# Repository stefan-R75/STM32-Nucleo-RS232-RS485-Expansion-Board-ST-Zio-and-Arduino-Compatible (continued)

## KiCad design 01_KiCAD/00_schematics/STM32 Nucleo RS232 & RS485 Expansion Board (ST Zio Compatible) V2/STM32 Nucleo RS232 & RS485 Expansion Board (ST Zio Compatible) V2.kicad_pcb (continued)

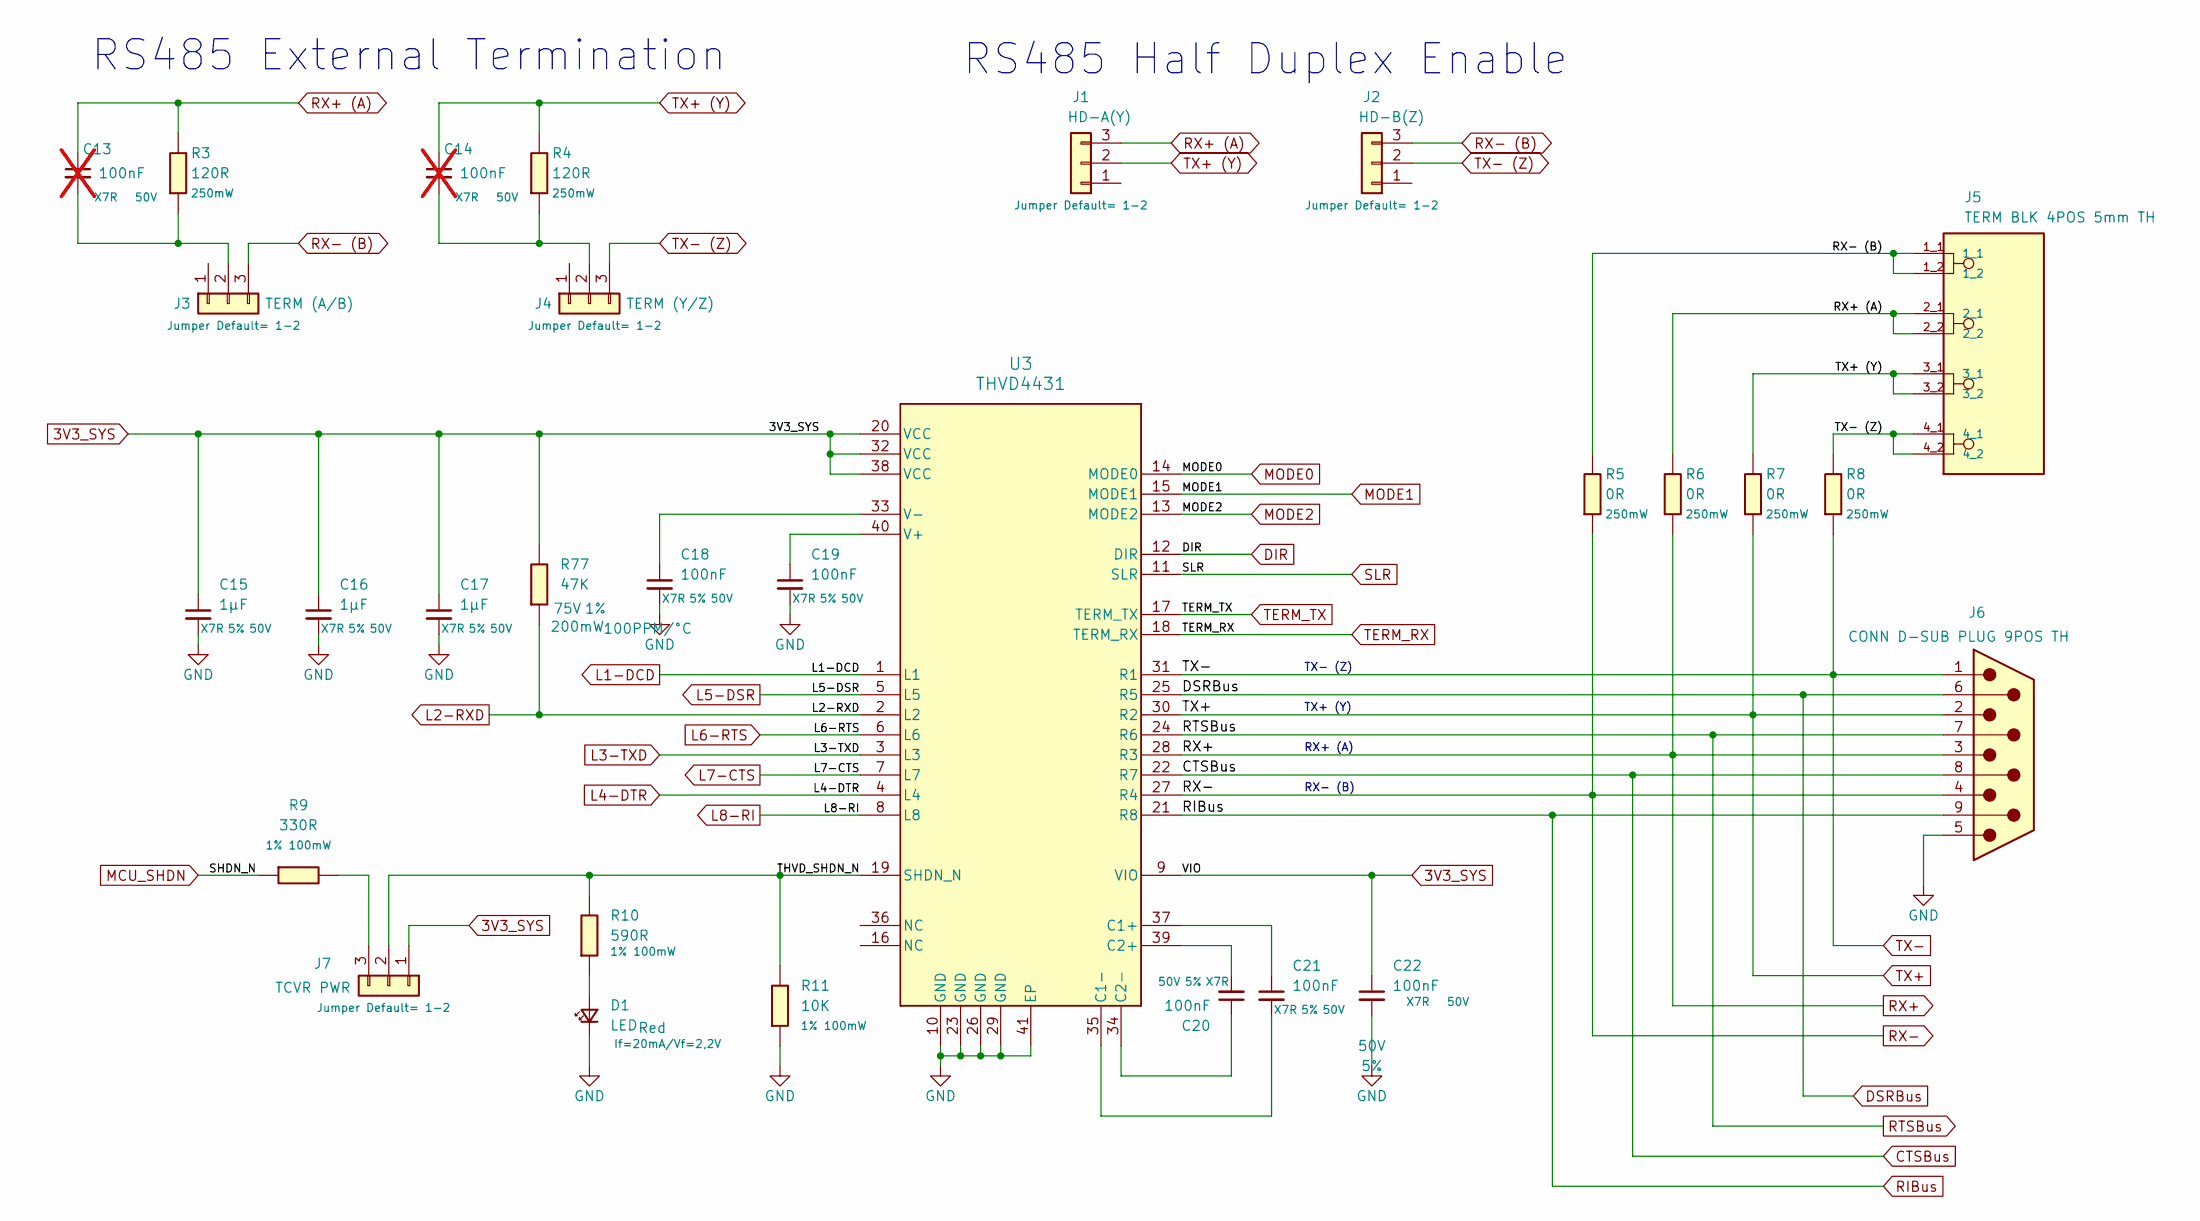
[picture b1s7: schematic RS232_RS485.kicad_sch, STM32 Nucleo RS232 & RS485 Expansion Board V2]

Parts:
C13, C14: 100nF; C_0805_2012Metric; Voltage Rating 50V; Voltage 50V; MPN C0805C104J5RACTU; LCSC C2167095; not fitted
C15, C16, C17: 1µF; C_1206_3216Metric; Voltage 50V; Tolerance 5%; MPN 12065C105JAT2A; LCSC C597503
C18, C19, C20, C21: 100nF; C_0805_2012Metric; Voltage 50V; Tolerance 5%; MPN C0805C104J5RACTU; LCSC C2167095
C22: 100nF; C_0805_2012Metric; Voltage Rating 50V; Voltage 50V; MPN C0805C104J5RACTU; LCSC C2167095
D1: LED; LED_0603_WRE; Voltage Rating If=20mA/Vf=2,2V; Voltage 2,2V; MPN IN-S63ATR; LCSC C6639626
J1: HD-A(Y); Samtec HTSW-103-07-F-S; Voltage Rating Jumper Default= 1-2; MPN HTSW-103-07-G-S; LCSC C5714562
J2: HD-B(Z); Samtec HTSW-103-07-F-S; Voltage Rating Jumper Default= 1-2; MPN HTSW-103-07-F-S; LCSC C5714562
J3: TERM (A/B); Samtec HTSW-103-07-F-S; Voltage Rating Jumper Default= 1-2; MPN HTSW-103-07-F-S; LCSC C5714562
J4: TERM (Y/Z); Samtec HTSW-103-07-F-S; Voltage Rating Jumper Default= 1-2; MPN HTSW-103-07-F-S; LCSC C5714562
J5: TERM BLK 4POS 5mm TH; PHOENIX_1190299; MPN 1190299; LCSC C3309834
J6: CONN D-SUB PLUG 9POS TH; CONN9_2301843-2_TEC; MPN 2301843-2; LCSC C591554
J7: TCVR PWR; Samtec HTSW-103-07-F-S; Voltage Rating Jumper Default= 1-2; MPN HTSW-103-07-F-S; LCSC C5714562
R3, R4: 120R; R_0603; Voltage Rating 250mW; MPN AC0603FR-7W120RL; LCSC C5552306
R5, R6, R7, R8: 0R; R_0805_2012Metric; Voltage Rating 250mW; MPN CRCW08050000Z0EAHP; LCSC C844811
R9: 330R; R_0603; Voltage Rating 1% 100mW; MPN AC0603FR-7W330RL; LCSC C513549
R10: 590R; R_0603; Voltage Rating 1% 100mW; MPN AC0603FR-07590RL; LCSC C227973
R11: 10K; R_0603; Voltage Rating 1% 100mW; MPN AC0603FR-7W10KL; LCSC C20142011
R77: 47K; R_0603; Voltage 75V; Tolerance 1%; MPN AC0603FR-7W47KL; LCSC C6732920
U3: THVD4431; RHA0040R-MFG; MPN THVD4431RHAR; LCSC C22445427

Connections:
3V3_SYS: C15.1, C16.1, C17.1, C22.1, J7.1, R77.1, U3.9 (VIO), U3.20 (VCC), U3.32 (VCC), U3.38 (VCC); also elsewhere on the board
/RS232 & RS485 Tranceiver/THVD_SHDN_N: J7.2, R10.1, R11.1, U3.19 (SHDN_N)
CTSBus: J6.8, U3.22 (R7); also elsewhere on the board
DIR: U3.12 (DIR); also elsewhere on the board
DSRBus: J6.6, U3.25 (R5); also elsewhere on the board
GND: C15.2, C16.2, C17.2, C18.2, C19.2, C22.2, D1.1 (K), J6.5, R11.2, U3.10 (GND), U3.23 (GND), U3.26 (GND), U3.29 (GND), U3.41 (EP); also elsewhere on the board
L1-DCD: U3.1 (L1); also elsewhere on the board
L2-RXD: R77.2, U3.2 (L2); also elsewhere on the board
L3-TXD: U3.3 (L3); also elsewhere on the board
L4-DTR: U3.4 (L4); also elsewhere on the board
L5-DSR: U3.5 (L5); also elsewhere on the board
L6-RTS: U3.6 (L6); also elsewhere on the board
L7-CTS: U3.7 (L7); also elsewhere on the board
L8-RI: U3.8 (L8); also elsewhere on the board
MCU_SHDN: R9.2; also elsewhere on the board
MODE0: U3.14 (MODE0); also elsewhere on the board
MODE1: U3.15 (MODE1); also elsewhere on the board
MODE2: U3.13 (MODE2); also elsewhere on the board
unnamed: D1.2 (A), R10.2
unnamed: C13.2, J3.2, R3.2
unnamed: C14.2, J4.2, R4.2
unnamed: J7.3, R9.1
unnamed: C21.1, U3.37 (C1+)
unnamed: C21.2, U3.35 (C1-)
unnamed: C20.2, U3.39 (C2+)
unnamed: C20.1, U3.34 (C2-)
unnamed: C19.1, U3.40 (V+)
unnamed: C18.1, U3.33 (V-)
RIBus: J6.9, U3.21 (R8); also elsewhere on the board
RTSBus: J6.7, U3.24 (R6); also elsewhere on the board
RX+: J6.3, R6.2, U3.28 (R3); also elsewhere on the board
RX+ (A): C13.1, J1.3, J5.2_1, J5.2_2, R3.1, R6.1; also elsewhere on the board
RX-: J6.4, R5.2, U3.27 (R4); also elsewhere on the board
RX- (B): J2.3, J3.3, J5.1_1, J5.1_2, R5.1; also elsewhere on the board
SLR: U3.11 (SLR); also elsewhere on the board
TERM_RX: U3.18 (TERM_RX); also elsewhere on the board
TERM_TX: U3.17 (TERM_TX); also elsewhere on the board
TX+: J6.2, R7.2, U3.30 (R2); also elsewhere on the board
TX+ (Y): C14.1, J1.2, J5.3_1, J5.3_2, R4.1, R7.1; also elsewhere on the board
TX-: J6.1, R8.2, U3.31 (R1); also elsewhere on the board
TX- (Z): J2.2, J4.3, J5.4_1, J5.4_2, R8.1; also elsewhere on the board

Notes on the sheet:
RX- (B)
TX- (Z)
RX+ (A)
TX+ (Y)
RS485 Half Duplex Enable
RS485 External Termination

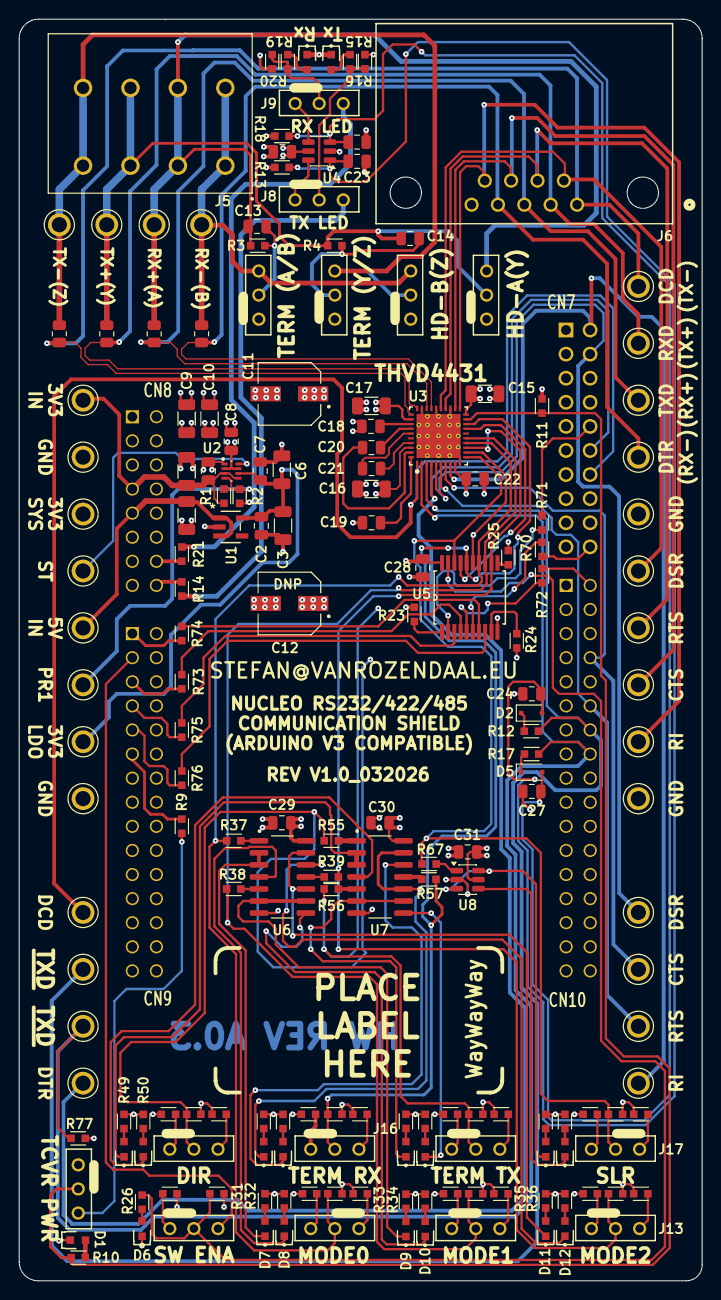
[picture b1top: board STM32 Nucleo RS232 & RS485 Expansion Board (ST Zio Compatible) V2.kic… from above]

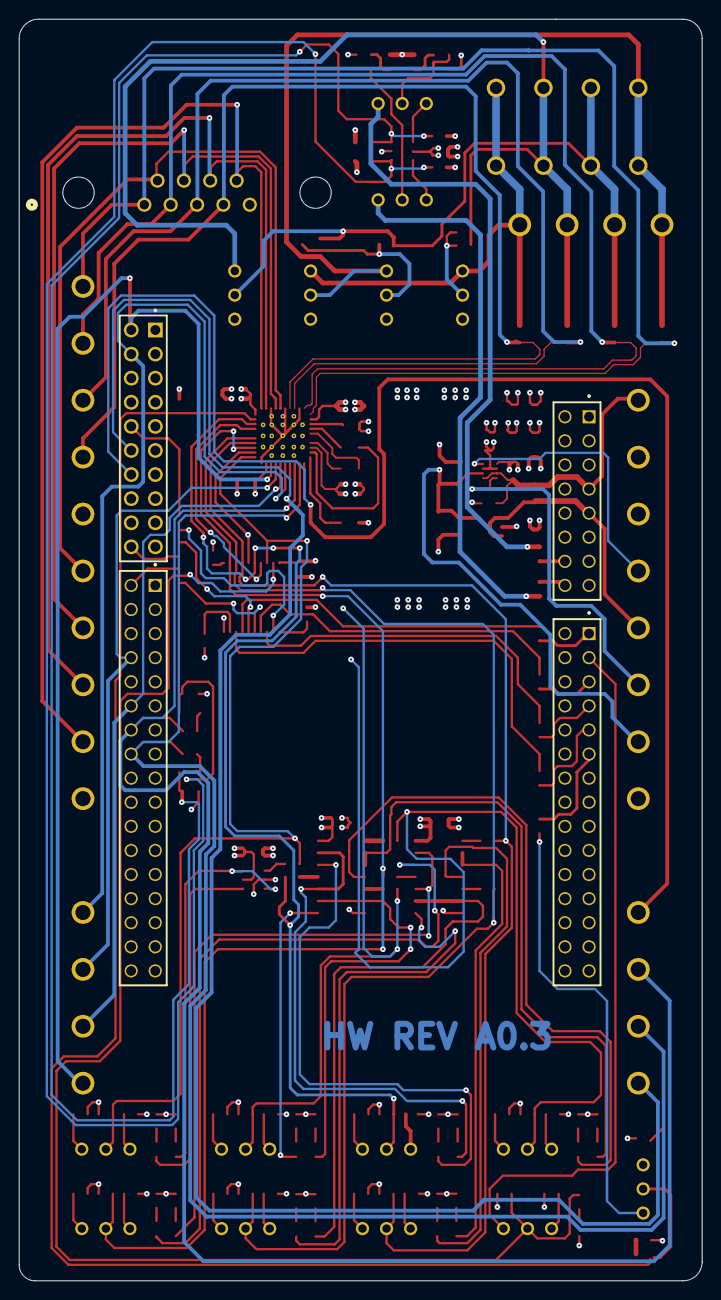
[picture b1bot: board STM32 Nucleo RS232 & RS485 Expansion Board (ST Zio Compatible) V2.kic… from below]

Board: 4 copper layers, 72.0 x 133.0 mm, 187 parts (4 on the bottom side), 130 nets.

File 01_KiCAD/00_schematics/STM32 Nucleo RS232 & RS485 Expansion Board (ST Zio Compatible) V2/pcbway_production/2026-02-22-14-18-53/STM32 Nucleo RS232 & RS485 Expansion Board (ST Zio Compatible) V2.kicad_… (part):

Designator,Quantity,Value,Footprint,Package,MPN,DNP,Mount_Type,Description,Manufacturer,LCSC,Type,Dielectric,Voltage,Tolerance,Mouser PN,Voltage Rating,PROD_ID,Color,MF,Description_1,Price,Check_prices,SnapEDA_Link,MP,Availability,MANUFACTURER,MAXIMUM_PACKAGE_HEIGHT,STANDARD,PARTREV,Purchase-URL,SNAPEDA_PN,Series
C1,1,1µF,C_1206_3216Metric,1206,12065C105JAT2A,Yes,smt,1uF ±5% 50V Ceramic Capacitor X7R 1206,Kyocera AVX,C597503,SMD,X7R,50V,5%,581-12065C105JAT2A,,,,,,,,,,,,,,,,,
C10,1,2µ2,C_1206_3216Metric,1206,C1206C225J5RECAUTO,Yes,smt,2.2uF X7R ±5% 50V 1206 Ceramic Capacitors RoHS,KEMET,C1513220,SMD,X7R,50V,5%,80-C1206C225J5RECAUT,,,,,,,,,,,,,,,,,
C11,1,47µF,CAP_EEEFT1H470AP,"SMD,D6.3xL5.8mm",EEEFT1H470AP,Yes,smt,47uF ±20% 50V Aluminum Electrolytic Capacitors 2000hrs@105℃,PANASONIC,C92059,SMD,20%,50V,20%,667-EEE-FT1H470AP,50V,,,,,,,,,,,,,,,,
C15,1,1µF,C_1206_3216Metric,1206,12065C105JAT2A,Yes,smt,1uF ±5% 50V Ceramic Capacitor X7R 1206,Kyocera AVX,C597503,SMD,X7R,50V,5%,581-12065C105JAT2A,,CAP-00810,,,,,,,,,,,,,,,
C16,1,1µF,C_1206_3216Metric,1206,12065C105JAT2A,Yes,smt,1uF ±5% 50V Ceramic Capacitor X7R 1206,Kyocera AVX,C597503,SMD,X7R,50V,5%,581-12065C105JAT2A,,CAP-00810,,,,,,,,,,,,,,,
C17,1,1µF,C_1206_3216Metric,1206,12065C105JAT2A,Yes,smt,1uF ±5% 50V Ceramic Capacitor X7R 1206,Kyocera AVX,C597503,SMD,X7R,50V,5%,581-12065C105JAT2A,,CAP-00810,,,,,,,,,,,,,,,
C18,1,100nF,C_0805_2012Metric,0805,C0805C104J5RACTU,Yes,smt,100nF ±5% 50V Ceramic Capacitor X7R 0805,KEMET,C2167095,SMD,X7R,50V,5%,80-C0805C104J5R,,CAP-00810,,,,,,,,,,,,,,,
C19,1,100nF,C_0805_2012Metric,0805,C0805C104J5RACTU,Yes,smt,100nF ±5% 50V Ceramic Capacitor X7R 0805,KEMET,C2167095,SMD,X7R,50V,5%,80-C0805C104J5R,,CAP-00810,,,,,,,,,,,,,,,
C2,1,100nF,C_0805_2012Metric,0805,C0805C104J5RACTU,Yes,smt,100nF ±5% 50V Ceramic Capacitor X7R 0805,KEMET,C2167095,SMD,X7R,50V,5%,80-C0805C104J5R,,,,,,,,,,,,,,,,,
C20,1,100nF,C_0805_2012Metric,0805,C0805C104J5RACTU,Yes,smt,100nF ±5% 50V Ceramic Capacitor X7R 0805,KEMET,C2167095,SMD,X7R,50V,5%,80-C0805C104J5R,,CAP-00810,,,,,,,,,,,,,,,
C21,1,100nF,C_0805_2012Metric,0805,C0805C104J5RACTU,Yes,smt,100nF ±5% 50V Ceramic Capacitor X7R 0805,KEMET,C2167095,SMD,X7R,50V,5%,80-C0805C104J5R,,CAP-00810,,,,,,,,,,,,,,,
C22,1,100nF,C_0805_2012Metric,0805,C0805C104J5RACTU,Yes,smt,100nF ±5% 50V Ceramic Capacitor X7R 0805,KEMET,C2167095,SMD,X7R,50V,5%,80-C0805C104J5R,50V,CAP-00810,,,,,,,,,,,,,,,
C23,1,470nF,C_0805_2012Metric,0805,08055C474JAT2A,Yes,smt,470nF ±5% 50V Ceramic Capacitor X7R 0805,Kyocera AVX,C14663,SMD,X7R,50V,5%,581-08055C474JAT2A,25V,CAP-00810,,,,,,,,,,,,,,,
C24,1,100nF,C_0805_2012Metric,0805,C0805C104J5RACTU,Yes,smt,100nF ±5% 50V Ceramic Capacitor X7R 0805,KEMET,C2167095,SMD,X7R,50V,5%,80-C0805C104J5R,50V,CAP-00810,,,,,,,,,,,,,,,
C25,1,100nF,C_0805_2012Metric,0805,C0805C104J5RACTU,Yes,smt,100nF ±5% 50V Ceramic Capacitor X7R 0805,KEMET,C2167095,SMD,X7R,50V,5%,80-C0805C104J5R,50V,CAP-00810,,,,,,,,,,,,,,,
C26,1,470nF,C_0805_2012Metric,0805,08055C474JAT2A,Yes,smt,470nF ±5% 50V Ceramic Capacitor X7R 0805,Kyocera AVX,C14663,SMD,X7R,50V,5%,581-08055C474JAT2A,25V,CAP-00810,,,,,,,,,,,,,,,
C27,1,100nF,C_0805_2012Metric,0805,C0805C104J5RACTU,Yes,smt,100nF ±5% 50V Ceramic Capacitor X7R 0805,KEMET,C2167095,SMD,X7R,50V,5%,80-C0805C104J5R,50V,CAP-00810,,,,,,,,,,,,,,,
C28,1,100nF,C_0805_2012Metric,0805,C0805C104J5RACTU,Yes,smt,100nF ±5% 50V Ceramic Capacitor X7R 0805,KEMET,C2167095,SMD,X7R,50V,5%,80-C0805C104J5R,50V,CAP-00810,,,,,,,,,,,,,,,
C29,1,100nF,C_0805_2012Metric,0805,C0805C104J5RACTU,Yes,smt,100nF ±5% 50V Ceramic Capacitor X7R 0805,KEMET,C2167095,SMD,X7R,50V,5%,80-C0805C104J5R,50V,CAP-00810,,,,,,,,,,,,,,,
C3,1,2µ2,C_1206_3216Metric,1206,C1206C225J5RECAUTO,Yes,smt,2.2uF X7R ±5% 50V 1206 Ceramic Capacitors RoHS,KEMET,C1513220,SMD,X7R,50V,5%,80-C1206C225J5RECAUT,,CAP-00810,,,,,,,,,,,,,,,
C30,1,100nF,C_0805_2012Metric,0805,C0805C104J5RACTU,Yes,smt,100nF ±5% 50V Ceramic Capacitor X7R 0805,KEMET,C2167095,SMD,X7R,50V,5%,80-C0805C104J5R,50V,CAP-00810,,,,,,,,,,,,,,,
C31,1,100nF,C_0805_2012Metric,0805,C0805C104J5RACTU,Yes,smt,100nF ±5% 50V Ceramic Capacitor X7R 0805,KEMET,C2167095,SMD,X7R,50V,5%,80-C0805C104J5R,50V,CAP-00810,,,,,,,,,,,,,,,
C4,1,1µF,C_1206_3216Metric,1206,12065C105JAT2A,Yes,smt,1uF ±5% 50V Ceramic Capacitor X7R 1206,Kyocera AVX,C597503,SMD,X7R,50V,5%,581-12065C105JAT2A,,,,,,,,,,,,,,,,,
C5,1,100nF,C_0805_2012Metric,0805,C0805C104J5RACTU,Yes,smt,100nF ±5% 50V Ceramic Capacitor X7R 0805,KEMET,C2167095,SMD,X7R,50V,5%,80-C0805C104J5R,,,,,,,,,,,,,,,,,
C6,1,1µF,C_1206_3216Metric,1206,12065C105JAT2A,Yes,smt,1uF ±5% 50V Ceramic Capacitor X7R 1206,Kyocera AVX,C597503,SMD,X7R,50V,5%,581-12065C105JAT2A,,,,,,,,,,,,,,,,,
C7,1,100nF,C_0805_2012Metric,0805,C0805C104J5RACTU,Yes,smt,100nF ±5% 50V Ceramic Capacitor X7R 0805,KEMET,C2167095,SMD,X7R,50V,5%,80-C0805C104J5R,50V,CAP-00810,,,,,,,,,,,,,,,
C8,1,100nF,C_0805_2012Metric,0805,C0805C104J5RACTU,Yes,smt,100nF ±5% 50V Ceramic Capacitor X7R 0805,KEMET,C2167095,SMD,X7R,50V,5%,80-C0805C104J5R,,CAP-00810,,,,,,,,,,,,,,,
C9,1,1µF,C_1206_3216Metric,1206,12065C105JAT2A,Yes,smt,1uF ±5% 50V Ceramic Capacitor X7R 1206,Kyocera AVX,C597503,SMD,X7R,50V,5%,581-12065C105JAT2A,,,,,,,,,,,,,,,,,
CN10,1,SSW-117-23-G-D,SAMTEC_SSW-117-23-F-D,"Through Hole,P=2.54mm",SSW-117-23-G-D,Yes,tht,Female Header 34 Position 2.54mm Pitch Dual Row Through Hole -55℃~+125℃,Samtec,C6501751,THT,,,,200-SSW11723GD,,,,,,,,,,,,,,,,,
CN7,1,SSW-110-23-G-D,SAMTEC_SSW-110-23-X-D,"Through Hole,P=2.54mm",SSW-110-23-G-D,Yes,tht,Female Header 20 Position 2.54mm Pitch Dual Row Through Hole -55℃~+125℃,Samtec,C6236460,THT,,,,200-SSW11023GD,,,,,,,,,,,,,,,,,
CN8,1,SSW-108-23-G-D,SAMTEC_SSW-108-23-F-D,"Through Hole,P=2.54mm",SSW-108-23-G-D,Yes,tht,Female Header 16 Position 2.54mm Pitch Dual Row Through Hole -55℃~+125℃,Samtec,C7019040,THT,,,,200-SSW10823GD,,,,,,,,,,,,,,,,,
CN9,1,SSW-115-23-G-D,SAMTEC_SSW-115-23-F-D,"Through Hole,P=2.54mm",SSW-115-23-G-D,Yes,tht,Female Header 30 Position 2.54mm Pitch Dual Row Through Hole -55℃~+125℃,Samtec,C7089189,THT,,,,200-SSW11523GD,,,,,,,,,,,,,,,,,
D1,1,LED,LED_0603_WRE,0603,IN-S63ATR,Yes,smt,636nm 120° 20mA Red 2.2V 0603 LED Indication - Discrete RoHS,Inolux,C6639626,SMD,,"2,2V",,743-S63ATR,"If=20mA/Vf=2,2V ",LED-,Red,,,,,,,,,,,,,,
D10,1,LED,LED_0603_WRE,0603,IN-S63AT5G,Yes,smt,Emerald Green 530nm LED Indication - Discrete 2.7V 0603,Inolux,C5656662,SMD,,"2,7V",,743-IN-S63AT5G,"If=25mA/Vf=2,7V ",LED-,Green,,,,,,,,,,,,,,
D11,1,LED,LED_0603_WRE,0603,IN-S63AT5A,Yes,smt,Amber 609nm LED Indication - Discrete 2V 0603,Inolux,C5656657,SMD,,"2,0V",,743-IN-S63AT5A,"If=25mA/Vf=2,0V ",LED-,Amber,,,,,,,,,,,,,,
D12,1,LED,LED_0603_WRE,0603,IN-S63AT5G,Yes,smt,Emerald Green 530nm LED Indication - Discrete 2.7V 0603,Inolux,C5656662,SMD,,"2,7V",,743-IN-S63AT5G,"If=25mA/Vf=2,7V ",LED-,Green,,,,,,,,,,,,,,
D13,1,LED,LED_0603_WRE,0603,IN-S63AT5A,Yes,smt,Amber 609nm LED Indication - Discrete 2V 0603,Inolux,C5656657,SMD,,"2,0V",,743-IN-S63AT5A,"If=25mA/Vf=2,0V ",LED-,Amber,,,,,,,,,,,,,,
D14,1,LED,LED_0603_WRE,0603,IN-S63AT5G,Yes,smt,Emerald Green 530nm LED Indication - Discrete 2.7V 0603,Inolux,C5656662,SMD,,"2,7V",,743-IN-S63AT5G,"If=25mA/Vf=2,7V ",LED-,Green,,,,,,,,,,,,,,
D15,1,LED,LED_0603_WRE,0603,IN-S63AT5A,Yes,smt,Amber 609nm LED Indication - Discrete 2V 0603,Inolux,C5656657,SMD,,"2,0V",,743-IN-S63AT5A,"If=25mA/Vf=2,0V ",LED-,Amber,,,,,,,,,,,,,,
D16,1,LED,LED_0603_WRE,0603,IN-S63AT5G,Yes,smt,Emerald Green 530nm LED Indication - Discrete 2.7V 0603,Inolux,C5656662,SMD,,"2,7V",,743-IN-S63AT5G,"If=25mA/Vf=2,7V ",LED-,Green,,,,,,,,,,,,,,
D17,1,LED,LED_0603_WRE,0603,IN-S63AT5A,Yes,smt,Amber 609nm LED Indication - Discrete 2V 0603,Inolux,C5656657,SMD,,"2,0V",,743-IN-S63AT5A,"If=25mA/Vf=2,0V ",LED-,Amber,,,,,,,,,,,,,,
D18,1,LED,LED_0603_WRE,0603,IN-S63AT5G,Yes,smt,Emerald Green 530nm LED Indication - Discrete 2.7V 0603,Inolux,C5656662,SMD,,"2,7V",,743-IN-S63AT5G,"If=25mA/Vf=2,7V ",LED-,Green,,,,,,,,,,,,,,
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
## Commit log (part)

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2026-02-04 initial commit
    initial commit
2026-02-04 Removed LED
    LED verwijderd dat gebruikt werd voor GitHub Test
2026-02-04 Add THVD4431 & Phoenic 4-p connector
    Added the THVD4431 dual Tranceiver Chip and modified schematic symbol.
    Added the RS485 Phoenix Contact connector (pn 1190299)
2026-02-04 Added SubD 9-P connector
    Added the RS232 SubD connector
2026-02-04 Added components
    Added R1 - R4 0R pass-through resistors for RS485 data lines to seperate them from RS232 Net
    Added capacitors C1+ and C2+ for charge pump
    Completed table on root page for THVD4431 and ZIO Connector Pin Layout
2026-02-05 Complemented descriptions
    Complemented the RS232, RS485 and THVD4431 description table on the Root page
2026-02-05 Added SHDN logic
    Added the SHDN pin logic to have both hardware control and software control vor activating the THVD4431
2026-02-06 Added Dual Voltage Input
    Added Dual Voltage Auto Select Input drawings. Added new hierarchical sheet with new pagenumber one. All other pages have been moved up by 1.
2026-02-07 Added components and change device
    Added dual Schmidt trigger input SN74LVC2G14DBV for LED Rx and Tx control.
    Changed sn74hcs245 for alternate part sn74lvc245a for larger footprint and better availability with LCSC.
    Difference is sn74lvc245a has no Schmidt-trigger inputs but instead just normal inputs. Fot details see dataseet. Both devices use exact same pin number and configuration except sn74lvc245a has no th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
2026-02-08 Finisching touches to schematics
    Finalizing the schematics and double-check all connections throughout the different sheets.
2026-02-08 Finishing up the schematic aand created the board outline
    Made some finishing touches to the schematic, updated all the symbol footprints and started to create the board.
    Added missing 3D models for Phoenix 4-p RS485 connector and RS232 connector, also for Inolux LED.
2026-02-09 Corrected RS485 connector layout
    Corrected the layout and connections to Phoenix Contacts connector J1 so pairs are next to eachother and simplyfied the board layout to better match the THVD4431 connections.
    Added some 3D models to the testpoints TP10, TP12, TP14 and TP16. Made color-coding for the RS485 pairs so they are easily identified as pairs belong to eachother.
2026-02-09 Added 3D models for TI Devices
    Added 3D models for the TI SN74LVC245A and THVD4431 devices
2026-02-09 Capacitor change
    Changed designator values for C1 t/m C7 so it is more logical on the sheet.
    Changed capacittor C7 from 100µF to lower part of 47µF because of mechanical reasons. Old capacitor was too high and new capacitor of 47µ is just about 5-6mm in height
2026-02-10 Updated footprints and added components to PCB
    Added some additional components to the board. Changed the footprint of the 3-pin Jumper so the bottom silkscreen text doesnlt overlap with the Dual Schmidt Trigger IC's SN74LVC2G14
2026-02-12 Changed to one-side only
    Changed design to fit all components to top-side of the board inseatd of to both top- and bottom side of the board. This simplifies the manufacturing process and saves costs during assembly.
2026-02-13 Changed schmitt trigger
    changed the schmitt trigger for hex-schmitt trigger variant to simpify design and reduce components
2026-02-13 Updated PCB
    Updated PCB with components layout and routing tracks.
2026-02-14 Added half-duplex jumpers
    Addres jumpers for hardware RS485 half-duplex configuration combining signals A(Y) & B(Z). Finalising testpoints and added 3D models for each test-point color.
    -Green = logic side
    -Blue = connector side
    Made some minor changed to layout for test signals clarification (THVD4431 sheet)
2026-02-15 Finalizing roting
    Made some final routings and updated Netlist name on the schematics for some of the RS232 testpoints.
2026-02-15 Finalizing PCB Design
    Finalizing track routing on PCB and run DRC. Made some minor silkscreen adjustments.
2026-02-17 Complete redesign
    Redesigned the complete board. Added hardware termination jumpers for 1120R resistors for RS485. Changes footprint, package size and simplified values between capacitors.
    Still need to re-route the entire board :-(
2026-02-18 Updating routing
    Update routing tracks and placing and re-ordering components on the board.
2026-02-19 Small changes to schematics & PCB work
    Made some minor adjustments to the schematics, updated the PCB accordingly.
    Placed all the components on the board and did some of the routing.
    Updated the 3D models of all the components.
2026-02-20 Finalizing board layout & routing
    Set HW Revision of board to: HW REV A0.1 and placed this as copper text on the back of the PCB.
    Run DRC to see any critical errors. Resolved some minor silkscreen issues with overlapping text.
2026-02-21 Updated components
    Updated components descriptions and partnumbers of C1, C2, C3, U1, TP1, TP2 and TP3
2026-02-21 Final revision checkup
    After BOM-update and corrected some footprints and package sizes for resistors and capacitors, updated the PCB to "HW REV A0.2" as final PCB layout. Need to run DRC check before final approval.
2026-02-22 Updated PCB Layout
    Moved the 4x RS485 testpoints closer to the Phoenix connector so the longer testpoints don't interfere with the added LCD shield when stacked together.
2026-02-22 Updated PCB
    Re-aligned all testpoints. Set fixed distance of 6mm from each testpoint to neighbour one. Set board outline to match exactly the dimensions of 133x72mm
2026-02-24 Changed to HR_REVA0.3
    Updates design to PCB HW-REVA0.3 with the folowing changes:
    CL_HW_2026_0001
    Replaced text on silkscreen D3=>RX and D4=>TX.
    CL_HW_2026_0002
    Changed MCU_SHDN pin for THVD4431 from CN9-30 to CN9-11 to make it also Arduino compatible
2026-02-24 Finilizing HW_REVA0.3
    See also CL_HW_2026_0003
    Added pull-up resistor to L2 on TI advise
2026-02-25 board setup
2026-02-25 Siklscreen update
    Found some late issues with the silkscreen tekst.
    Corrected "5V EXT" to "5V IN", matching the 3V3 IN testpoint.
    Corrected the "5V EXT" testpoint to the correct name "3V3 LDO".
    Fixed overall text positions to be a minimum of 1mm height and 0.2mm thickness. Corrected the BOM list for PCBWay Manufacturing and assembly. 137Ω resistor was wrongfully set as 137KΩ. Corrected this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
